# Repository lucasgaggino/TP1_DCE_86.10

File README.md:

# TP1_DCE_86.10

https://es.overleaf.com/read/jdksykzqdbtq

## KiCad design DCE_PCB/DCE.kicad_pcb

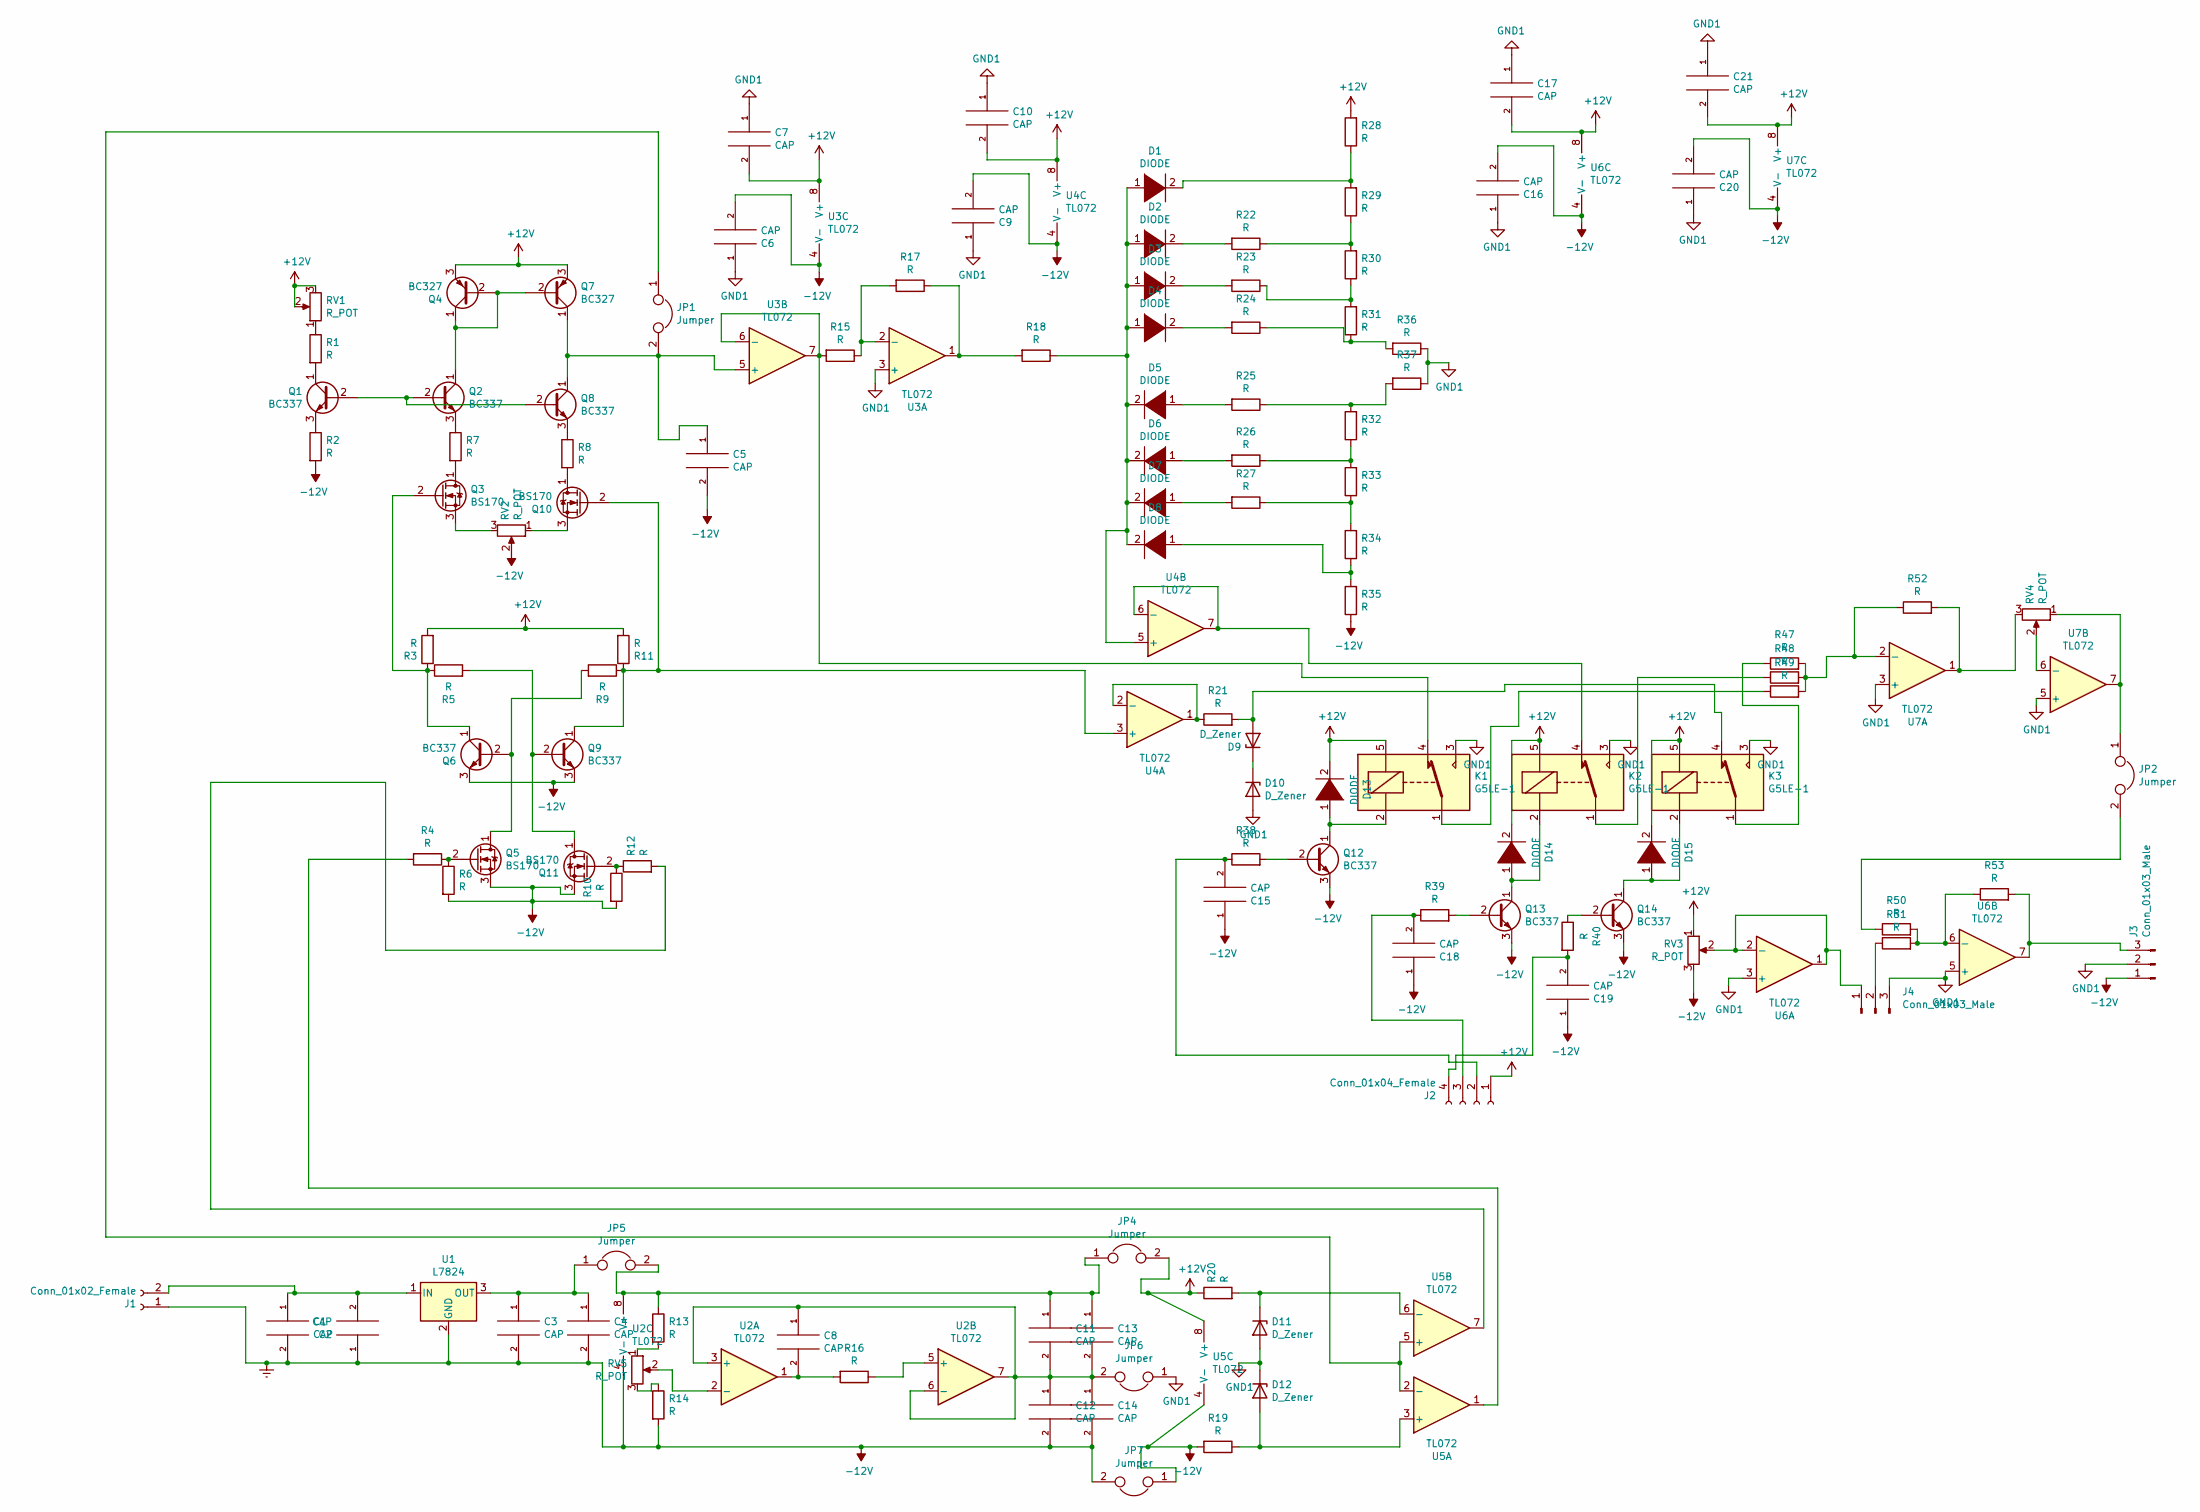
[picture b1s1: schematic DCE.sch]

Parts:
C1, C2, C4, C5, C6, C7, C8, C9, C10, C11, C12, C15, C16, C17, C18, C19, C20, C21: CAP; C_1206_3216Metric
C3, C13, C14: CAP; CP_Radial_D5.0mm_P2.00mm
D1, D2, D3, D4, D5, D6, D7, D8: DIODE; D_MiniMELF
D9, D10, D11, D12: D_Zener; D_DO-35_SOD27_P2.54mm_Vertical_KathodeUp
D13, D14, D15: DIODE; D_DO-41_SOD81_P10.16mm_Horizontal
J1: Conn_01x02_Female; PhoenixContact_MSTBA_2,5_2-G-5,08_1x02_P5.08mm_Horizontal
J2: Conn_01x04_Female; PhoenixContact_MSTBA_2,5_4-G-5,08_1x04_P5.08mm_Horizontal
J3, J4: Conn_01x03_Male; PinHeader_1x03_P2.54mm_Vertical
JP1, JP2, JP4, JP5, JP6, JP7: Jumper; SolderJumper-2_P1.3mm_Open_Pad1.0x1.5mm
K1, K2, K3: G5LE-1; Relay_SPDT_Omron-G5LE-1
Q1, Q2, Q6, Q8, Q9, Q12, Q13, Q14: BC337; TO-92_Inline
Q3, Q5, Q10, Q11: BS170; TO-92_Inline
Q4, Q7: BC327; TO-92_Inline
R1, R2, R3, R4, R5, R6, R7, R8, R9, R10, R11, R12, R13, R14, R15, R16, R17, R18, R19, R20, R21, R22, R23, R24, R25, R26, R27, R28, R29, R30, R31, R32, R33, R34, R35, R36, R37, R38, R39, R40, R47, R48, R49, R50, R51, R52, R53: R; R_1206_3216Metric
RV1, RV2, RV3, RV4: R_POT; Potentiometer_Piher_T-16H_Single_Horizontal
RV5: R_POT; Potentiometer_Bourns_3296W_Vertical
U1: L7824; TO-220-3_Vertical
U2, U3, U4, U5, U6, U7: TL072; PowerIntegrations_SO-8

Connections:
+12V: C7.2, C10.2, C17.2, C21.2, D13.2 (A), D14.2 (A), D15.2 (A), J2.1, JP4.2, K1.5, K2.5, K3.5, Q4.3 (E), Q7.3 (E), R3.2, R11.2, R20.1, R28.2, RV1.2, RV1.3, RV3.1, U3.8 (V+), U4.8 (V+), U5.8 (V+), U6.8 (V+), U7.8 (V+)
-12V: C1.2, C2.1, C3.2, C4.2, C5.2, C6.2, C9.2, C12.2, C14.2, C15.1, C16.2, C18.1, C19.1, C20.2, J1.1, J3.1, JP7.1, JP7.2, Q5.3 (S), Q6.3 (E), Q9.3 (E), Q11.3 (S), Q12.3 (E), Q13.3 (E), Q14.3 (E), R2.2, R6.2, R10.2, R14.2, R19.2, R35.1, RV2.2, RV3.3, U1.2 (GND), U2.4 (V-), U3.4 (V-), U4.4 (V-), U5.4 (V-), U6.4 (V-), U7.4 (V-)
GND1: C6.1, C7.1, C9.1, C10.1, C16.1, C17.1, C20.1, C21.1, D10.2 (A), D11.2 (A), D12.1 (K), J3.2, J4.3, JP6.1, K1.3, K2.3, K3.3, R36.1, R37.1, U3.3 (+), U6.3 (+), U6.5 (+), U7.3 (+), U7.5 (+)
unnamed: C1.1, C2.2, J1.2, U1.1 (IN)
unnamed: C3.1, C4.1, JP5.1, U1.3 (OUT)
unnamed: C5.1, JP1.2, Q7.1 (C), Q8.1 (C), U3.5 (+)
unnamed: C8.2, R16.2, U2.1
unnamed: C11.1, C13.1, JP4.1, JP5.2, R13.1, U2.8 (V+)
unnamed: C8.1, C11.2, C12.1, C13.2, C14.1, JP6.2, U2.3 (+), U2.6 (-), U2.7
unnamed: C15.2, J2.2, R38.1
unnamed: C18.2, J2.3, R39.1
unnamed: C19.2, J2.4, R40.2
unnamed: D1.1 (K), D2.1 (K), D3.1 (K), D4.1 (K), D5.2 (A), D6.2 (A), D7.2 (A), D8.2 (A), R18.1, U4.5 (+)
unnamed: D1.2 (A), R28.1, R29.2
unnamed: D2.2 (A), R22.2
unnamed: D3.2 (A), R23.2
unnamed: D4.2 (A), R24.2
unnamed: D5.1 (K), R25.2
unnamed: D6.1 (K), R26.2
unnamed: D7.1 (K), R27.2
unnamed: D8.1 (K), R34.1, R35.2
unnamed: D9.2 (A), K3.4, R21.2
unnamed: D9.1 (K), D10.1 (K)
unnamed: D11.1 (K), R20.2, U5.6 (-)
unnamed: D12.2 (A), R19.1, U5.3 (+)
unnamed: D13.1 (K), K1.2, Q12.1 (C)
unnamed: D14.1 (K), K2.2, Q13.1 (C)
unnamed: D15.1 (K), K3.2, Q14.1 (C)
unnamed: J3.3, R53.2, U6.7
unnamed: J4.1, RV3.2, U6.1, U6.2 (-)
unnamed: J4.2, R51.1
unnamed: JP1.1, U5.2 (-), U5.5 (+)
unnamed: JP2.1, RV4.1, U7.7
unnamed: JP2.2, R50.1
unnamed: K1.1, R49.1
unnamed: K1.4, R15.2, U3.6 (-), U3.7
unnamed: K2.1, R48.1
unnamed: K2.4, U4.6 (-), U4.7
unnamed: K3.1, R47.1
unnamed: Q1.1 (C), R1.2
unnamed: Q1.2 (B), Q2.2 (B), Q8.2 (B)
unnamed: Q1.3 (E), R2.1
unnamed: Q2.1 (C), Q4.1 (C), Q4.2 (B), Q7.2 (B)
unnamed: Q2.3 (E), R7.1
unnamed: Q3.1 (D), R7.2
unnamed: Q3.2 (G), Q6.1 (C), R3.1, R5.1
unnamed: Q3.3 (S), RV2.3
unnamed: Q5.1 (D), Q6.2 (B), R9.2
unnamed: Q5.2 (G), R4.1, R6.1
unnamed: Q8.3 (E), R8.1
unnamed: Q10.1 (D), R8.2
unnamed: Q9.1 (C), Q10.2 (G), R9.1, R11.1, U4.3 (+)
unnamed: Q10.3 (S), RV2.1
unnamed: Q9.2 (B), Q11.1 (D), R5.2
unnamed: Q11.2 (G), R10.1, R12.1
unnamed: Q12.2 (B), R38.2
unnamed: Q13.2 (B), R39.2
unnamed: Q14.2 (B), R40.1
unnamed: R1.1, RV1.1
unnamed: R4.2, U5.1
unnamed: R12.2, U5.7
unnamed: R13.2, RV5.1
unnamed: R14.1, RV5.3
unnamed: R15.1, R17.2, U3.2 (-)
unnamed: R16.1, U2.5 (+)
unnamed: R17.1, R18.2, U3.1
unnamed: R21.1, U4.1, U4.2 (-)
unnamed: R22.1, R29.1, R30.2
unnamed: R23.1, R30.1, R31.2
unnamed: R24.1, R31.1, R36.2
unnamed: R25.1, R32.2, R37.2
unnamed: R26.1, R32.1, R33.2
unnamed: R27.1, R33.1, R34.2
unnamed: R47.2, R48.2, R49.2, R52.1, U7.2 (-)
unnamed: R50.2, R51.2, R53.1, U6.6 (-)
unnamed: R52.2, RV4.3, U7.1
unnamed: RV4.2, U7.6 (-)
unnamed: RV5.2, U2.2 (-)

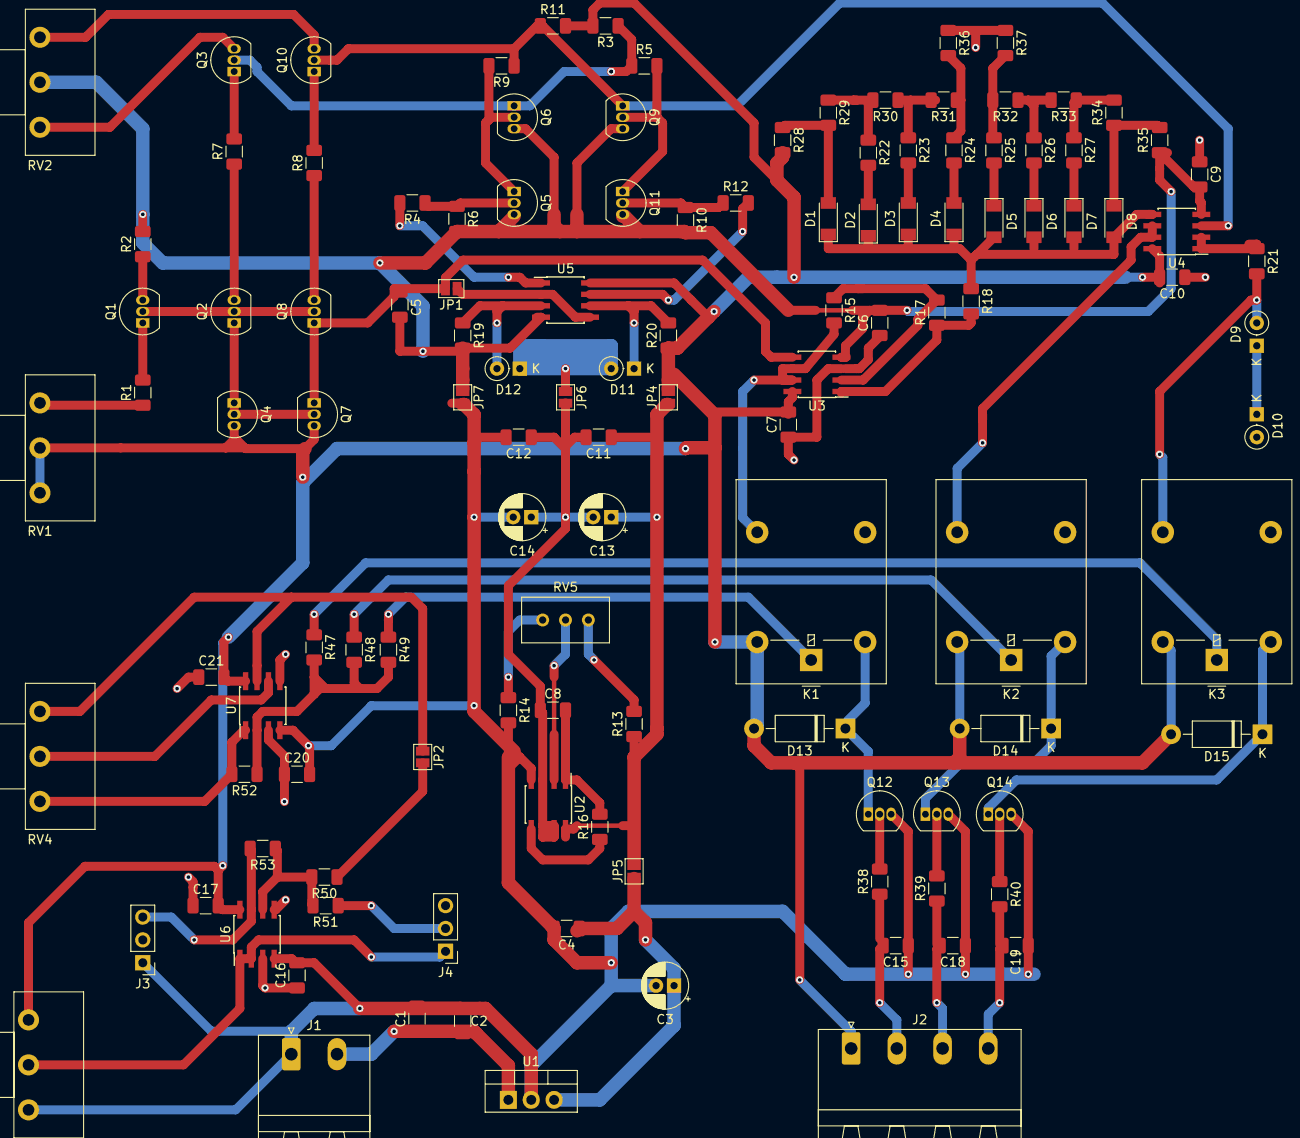
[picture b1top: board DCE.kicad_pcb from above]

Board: 2 copper layers, 122 parts (0 on the bottom side), 78 nets.

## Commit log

2020-04-20 Creación de README
2020-04-20 Commit inicial
2020-04-20 Manejo de Gráficos
2020-04-21 Borrar archivo erroneo
2020-04-22 Gráficos especificaciones de ondas
2020-04-22 simulacion con ruptura
2020-04-29 diagrama en bloques esquematico
2020-04-29 diferenciacion de etapas y agregado de escalas basico
2020-04-29 Corrección del Factor de Distorsión y gráficos
2020-04-29 esquematico con capacitor extra
2020-05-07 Add files via upload
    Esquemático del método de ruptura, THD del 0,5%
2020-05-12 valores normalizados
    componentes calculados para cumplir los parametros pedidos y valores normalizados
2020-07-14 PCB_TP1
